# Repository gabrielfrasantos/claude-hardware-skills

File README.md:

# hardware-design-skills

**Sourced design rules and tested tools that let an AI agent design electronics in KiCad 10, from requirements to
fab files, without guessing.**

An agent asked to lay out a buck converter or pick decoupling will produce something plausible. Plausible isn't
good enough for a board: a wrong rule costs a respin. This repository gives the agent two things it lacks:

1. **Rules it can follow and you can check.** Every number cites its source (datasheet, app note, standard or fab
   capability page, by document ID and section). If a number has no source, it is marked *derived* with the
   arithmetic shown, or labelled *rule of thumb* or *house style*. Rules are vendor-neutral: they tell you which
   datasheet parameter to look up instead of copying one part family's value.
2. **Tools that work on real KiCad files.** Python scripts read and write `.kicad_sch` / `.kicad_pcb` directly and
   call `kicad-cli`. They generate the schematic, assign MCU pins, place parts, size net classes, set fab rules,
   copy vendor layouts, run gates and review the design. They run the same in an agent session, in a terminal and
   in CI.

The skills are not tied to a particular board, MCU family or vendor.

## Workflow

```mermaid
flowchart LR
  R[Requirements<br/>hardware-project] --> S[Schematic as code<br/>schematic-capture]
  S --> C[Circuit rules<br/>mcu / power / analog]
  C --> SIM[Simulation<br/>circuit-simulation]
  SIM --> P[Placement and pins<br/>pcb-placement]
  P --> N[Net classes, fab rules<br/>pcb-copper, pcb-design-rules]
  N --> L[Routing rules<br/>power / RF / high-speed / interface]
  L --> AR[Autoroute the rest<br/>pcb-routing]
  AR --> G[Gates: DRC, geometry, copper, assembly]
  G --> RV[Design review<br/>design-review + board-reviewer]
  RV --> F[Fab and assembly files<br/>hardware-project]
  V[Vendor reference layouts<br/>reference-block] -.-> P
```

Each phase ends at a gate the owner signs off. Requirements are traced to the firmware, and every decision is
logged.

## Skills

| Area | Skill | What it does |
|---|---|---|
| Project | [`hardware-project`](plugins/hardware-design/skills/hardware-project/SKILL.md) | Scaffolds a board repo (requirements traced to firmware, decision log, phase plan, reviewer agent). Checks traceability. Exports the review package, BOM, JLCPCB stock check, fab files, release package and visual diffs |
| Review | [`design-review`](plugins/hardware-design/skills/design-review/SKILL.md) | Runs every scripted check on a schematic or PCB in one command: decoupling, pull-ups, straps, voltage ratings, polarity, connector ESD, ERC/DRC, fab, geometry, net classes, assembly. A read-only reviewer agent then triages the findings against the datasheets |
| Schematic | [`schematic-capture`](plugins/hardware-design/skills/schematic-capture/SKILL.md) | Writes the schematic as Python and builds it into KiCad 10 the same way every time. Checks the netlist against intent, proves that drawing-only changes leave the circuit alone, and checks symbols against footprints and BOM fields |
| Circuits | [`mcu-circuit-design`](plugins/hardware-design/skills/mcu-circuit-design/SKILL.md) | Covers everything around any MCU: supplies, decoupling, reset/boot, clocks, debug, GPIO protection, ESD |
| | [`power-circuit-design`](plugins/hardware-design/skills/power-circuit-design/SKILL.md) | Covers input protection, buck/LDO rails, H-bridge and three-phase stages, gate drive, bus capacitors, current sensing, snubbers and thermal design |
| | [`analog-circuit-design`](plugins/hardware-design/skills/analog-circuit-design/SKILL.md) | Covers op-amps, references, ADC drive and sensor front ends: protection, noise, stability |
| | [`circuit-simulation`](plugins/hardware-design/skills/circuit-simulation/SKILL.md) | Builds an ngspice + Python suite from the schematic: loop stability, corners, transients, protection, noise, and a report |
| Layout | [`pcb-placement`](plugins/hardware-design/skills/pcb-placement/SKILL.md) | Builds or updates the board from the schematic without KiCad's window, places unlocked parts around the owner's locked anchors with simulated annealing, gates the result against assembly rules, and assigns MCU pins from the placement |
| | [`pcb-routing`](plugins/hardware-design/skills/pcb-routing/SKILL.md) | Autoroutes the non-critical nets with Freerouting, headless: writes the board as a Specctra DSN (no pcbnew), runs the router, adds its tracks and vias back |
| | [`pcb-copper`](plugins/hardware-design/skills/pcb-copper/SKILL.md) | Applies one standard net-class set (`PWR_4A`, `GND`, `DIFF_90`, `RF_50`, …). Sizes widths from current and clearances from voltage (IPC-2152 / IPC-2221) |
| | [`pcb-design-rules`](plugins/hardware-design/skills/pcb-design-rules/SKILL.md) | Sets board rules from fab profiles (JLCPCB, Seeed), turns on teardrops, records the stack-up, and gates shorts, clearance, geometry and copper. Keeps the silkscreen to readable references only |
| | [`power-pcb-layout`](plugins/hardware-design/skills/power-pcb-layout/SKILL.md) | Covers hot loops, gate drive, high-current copper, Kelvin sensing, thermal and isolation |
| | [`rf-layout`](plugins/hardware-design/skills/rf-layout/SKILL.md) | Covers 2.4 GHz radios (BLE, 802.15.4, Wi-Fi), chip-down or module: 50 Ω lines, matching, antennas, coexistence, certification |
| | [`high-speed-digital-layout`](plugins/hardware-design/skills/high-speed-digital-layout/SKILL.md) | Covers QSPI, SDRAM, DDR, SD/eMMC, RGB/MIPI/LVDS displays, cameras and clocks |
| | [`interface-layout`](plugins/hardware-design/skills/interface-layout/SKILL.md) | Covers USB, USB-C/PD, CAN, RS-485, Ethernet, isolated buses, connector ESD and shielding |
| | [`reference-block`](plugins/hardware-design/skills/reference-block/SKILL.md) | Copies a vendor's proven layout block (RF corner, NFC coil, power stage) onto your board, maps parts and nets, and checks the block stays intact |

## Install

The skills are packaged as a [Claude Code](https://code.claude.com) plugin marketplace (`hardware-skills`, one
plugin: `hardware-design`).

```
/plugin marketplace add gabrielfrasantos/hardware-design-skills
/plugin install hardware-design@hardware-skills
```

Skills load when a task matches their description. To call one by name, use e.g.
`/hardware-design:pcb-placement`. Releases are tagged `vX.Y.Z` (see the [changelog](CHANGELOG.md)). To update, run
`/plugin marketplace update hardware-skills`.

**For a whole team:** from the board repo's root, run this once and commit the `.claude/settings.json` it writes:

```bash
claude plugin marketplace add gabrielfrasantos/hardware-design-skills --scope project
```

**Other agents and plain use:** each skill is a `SKILL.md` (Markdown with YAML front matter) plus `scripts/`. The
rules-only skills (`*-circuit-design`, `*-layout`, `circuit-simulation`) are self-contained: zip the folder for
claude.ai, or point any agent that reads Agent Skills at it. The scripts are ordinary command-line tools with
`--help`. They don't need an agent.

## Quick start

The flow for a new board, as commands. In an agent session, ask for each step in words ("scaffold a board repo for a
motor controller", "review the board"), and the matching skill runs the same scripts. `$HW` is the absolute path
of `plugins/hardware-design/skills` in a checkout of this repository, so the commands still work after `cd` into the
board repo.

```bash
HW="$(pwd)/plugins/hardware-design/skills"   # run from the root of this repository's checkout

# 1. A board repo with requirements, decisions, phase gates and a reviewer agent
python3 $HW/hardware-project/scripts/scaffold.py ../my-board --name my-board --title "my-board: what it is" \
        --firmware owner/my-firmware --fab jlcpcb --layers 4
cd ../my-board            # then create hardware/my-board/my-board.kicad_pro in KiCad

# 2. Schematic as code, checked against the intended netlist
python3 $HW/schematic-capture/scripts/schgen.py build scripts/schgen/config.py
python3 $HW/schematic-capture/scripts/schgen.py check scripts/schgen/config.py

# 3. Net classes and fab rules on the KiCad project
python3 $HW/pcb-copper/scripts/netclasses.py apply hardware/my-board/my-board.kicad_pro
python3 $HW/pcb-design-rules/scripts/pcb_rules.py apply hardware/my-board/my-board.kicad_pro --fab jlcpcb --netclasses

# 4. Board from the schematic (no KiCad window needed), placement around your locked anchors, then the gates
python3 $HW/pcb-placement/scripts/sync.py hardware/my-board/my-board.kicad_pcb
python3 $HW/pcb-placement/scripts/place.py optimize hardware/my-board/my-board.kicad_pcb
python3 $HW/pcb-placement/scripts/place.py gate hardware/my-board/my-board.kicad_pcb
python3 $HW/pcb-routing/scripts/route.py run hardware/my-board/my-board.kicad_pcb --fetch --skip-nets 'GND|VM'   # after the critical nets
python3 $HW/pcb-design-rules/scripts/pcb_rules.py check hardware/my-board/my-board.kicad_pcb --report pcb-quality.md

# 5. Review everything into one findings file, then export for the fab
python3 $HW/design-review/scripts/review.py hardware/my-board --voltage VBAT=12.6
python3 $HW/hardware-project/scripts/export_jlcpcb.py
```

The generated `AGENTS.md` (imported by `CLAUDE.md`) lists every command and which skill covers each part of the
work.

## Worked example

[`examples/stepper-ble`](examples/stepper-ble/README.md) is a public board designed end to end with these skills: a
24 V stepper driver (DRV8711, eight external FETs) with Bluetooth LE (STM32WB55CG, PCB antenna) on JLCPCB 4-layer.
It has a schematic as code, the parts chosen from JLCPCB stock, the placement and MCU pin map, and every gate and the
design review run on it. It is placed but not routed. CI rebuilds its schematic and runs every gate on it with
KiCad 10 on each pull request, so the claims above can be checked on a board anyone can open.

## Requirements

| For | Needs |
|---|---|
| The tools | Python 3.10+, `pip install -r requirements.txt` (shapely, numpy, scipy, matplotlib) |
| DRC, ERC, netlists, imports, exports | KiCad **10 or later** (`kicad-cli`). Older files are refused: open and save them in KiCad 10 first |
| `circuit-simulation` | ngspice |
| `jlc_stock.py`, `fetch_datasheet.py` | Network access (JLCPCB/LCSC) |
| The test suite | None of the above beyond Python: tests use synthetic KiCad 10 files |

## How it's checked

- **Sources.** Each skill ends with its references.
  [`docs/research/best-practices-audit.md`](docs/research/best-practices-audit.md) audits the skills against
  primary sources and records what changed as a result.
- **Tests.** Every script has self-tests. CI runs them, a lint and the plugin validator on every pull request.
- **KiCad in CI.** The `example-board` job installs KiCad 10 with
  [kicad-bot](https://github.com/embedded-pro/kicad-bot) (ERC and DRC), rebuilds the example's schematic, checks it is
  the same circuit as the committed one, and runs every gate on the board.
- **Real boards.** The tools were measured on real boards (a power supply, a 50 V motor driver and a
  battery-powered robot controller). Each skill says what was measured, on what kind of board, and what wasn't.
- **Evals.** [`evals/`](evals/README.md) is a generic harness. It runs a board repo's own eval cases with and
  without the skills, scores the results against the owner's work, and plants known defects to score a review.
  Cases live in the board repos, not here.

## Status and limits

Version 0.x. The rules and tools are usable. The plan and its open phases are in [`docs/design.md`](docs/design.md).
Known limits:

- KiCad 10+ only. No KiCad 8/9 support, and no `pcbnew` (SWIG) code.
- Fab profiles exist for JLCPCB and Seeed only. Assembly rules exist for JLCPCB only. Other fabs need a profile in
  `pcb-design-rules/profiles/`.
- The RF rules cover 2.4 GHz only.
- Routing critical nets stays with the designer. `pcb-routing` autoroutes only the rest, with Freerouting (Java 25),
  and its result follows clearance and width, not the house style: expect hand tidying.
- `kicad-cli` has no *Update PCB from Schematic*; `pcb-placement`'s `sync.py` does it headless. It adds, updates,
  replaces and removes footprints and pad nets, matched to symbols by their link. It refuses to replace a footprint
  on the back side, and leaves outline, zones, net classes and copper on renamed nets (`pcb-design-rules`'
  `orphan_copper_nets`) to other tools or KiCad. The example board was first built with a short `pcbnew` script;
  `sync.py` reproduces it byte for byte (`pcb-placement` §0).
- Some IPC values are transcribed from secondary sources until the standards themselves are checked. Each skill
  marks which ones.

## Repository layout

```
.claude-plugin/marketplace.json        marketplace "hardware-skills"
plugins/hardware-design/
├── .claude-plugin/plugin.json         plugin "hardware-design"
├── agents/board-reviewer.md           read-only reviewer agent
└── skills/<skill>/                    SKILL.md, plus scripts/ and profiles/ where the skill has tools
docs/design.md                         plan and decisions (D1, D2, ...)
docs/research/                         audits and research notes
evals/                                 generic eval harness
```

## Contributing

Security issues: see [SECURITY.md](SECURITY.md).

The most useful contribution is a correction backed by a primary source. See [CONTRIBUTING.md](CONTRIBUTING.md) for
how rules are sourced, how scripts are tested and how commits become releases.

## License

[MIT](LICENSE). The skills cite vendor documents and standards without reproducing them; those documents remain
under their owners' terms. Vendor design files used with `reference-block` stay in your board repo's gitignored
`reference/` folder, under the vendor's licence.

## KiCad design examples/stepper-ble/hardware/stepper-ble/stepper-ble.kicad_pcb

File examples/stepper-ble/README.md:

# stepper-ble

A 24 V bipolar stepper driver with Bluetooth LE, designed from scratch with the `hardware-design` skills of this
repository and nothing else: the worked example. It is **placed, not routed** (D-027).

| | |
|---|---|
| Input | 24 V nominal, 30 V max, 2-pin terminal; 3 A fast fuse, reverse-polarity N-FET, SMAJ33A clamp |
| Motor | one bipolar stepper, 2.0 A peak per phase: DRV8711 + 8 x CSD18543Q3A, 0.1 ohm low-side sense, stall detection, NTC on the FETs |
| Logic | LMR36510 5 V buck OR-ed with USB VBUS, AP2112K 3.3 V |
| MCU, radio | STM32WB55CGU6 (SMPS mode, 32 MHz HSE, 32.768 kHz LSE), MLPF-WB55-01E3, TI SWRA117D PCB antenna with a DNP tuning pi |
| Interfaces | USB-C 2.0 full-speed sink with USBLC6, SWD on a Tag-Connect TC2030 land, two LEDs, a button |
| Board | 80 x 60 mm, 4 layers SIG/GND/GND/SIG (JLC04161H-7628, 1.6 mm), JLCPCB fab and assembly, IPC Class 2, 106 parts |

Contract: `docs/requirements.md` (26 requirements); intent: `docs/decisions.md` (27 decisions); status:
`docs/plan.md`. Every value on the schematic carries its source in a note on its sheet.

## Layout of this folder

```
scripts/make_library.py     project library: DRV8711 and MLPF symbols, MLPF land, two adapted KiCad footprints (D-016)
scripts/schgen/             the schematic as code: config.py, design/<sheet>.py, parts.py (the BOM), expected.json
scripts/make_board.py       board from KiCad's netlist with pcbnew: build/update, outline, stack-up, zones, placement
pin-data/                   pin-needs.txt (from the requirements, D-017) and pinmap.txt (pins.py, frozen D-014)
hardware/stepper-ble/       KiCad 10 project; placement-baseline.json is the accepted placement's gate metrics
bom/                        bom.csv, bom_jlc.csv (export_bom.py)
```

## Reproduce

From this folder, with KiCad 10 (`kicad-cli` and its `pcbnew` Python module) and `pip install -r ../../requirements.txt`:

```bash
HW=../../plugins/hardware-design/skills
export HW_PROJECT_ROOT=$PWD                    # the hardware-project scripts otherwise take the repository root
python3 scripts/make_library.py
python3 $HW/schematic-capture/scripts/schgen.py build scripts/schgen/config.py
python3 $HW/schematic-capture/scripts/schgen.py check scripts/schgen/config.py
python3 $HW/pcb-copper/scripts/netclasses.py assign hardware/stepper-ble/stepper-ble.kicad_pro
/usr/bin/python3 scripts/make_board.py build   # needs pcbnew: system Python
/usr/bin/python3 scripts/make_board.py place
python3 $HW/pcb-design-rules/scripts/pcb_rules.py apply hardware/stepper-ble/stepper-ble.kicad_pro --fab jlcpcb --netclasses
python3 $HW/pcb-copper/scripts/netclasses.py apply hardware/stepper-ble/stepper-ble.kicad_pro
python3 $HW/pcb-design-rules/scripts/silk.py apply hardware/stepper-ble/stepper-ble.kicad_pcb
```

The pin map was found with `pins.py assign ... --out pin-data/pinmap.txt` after a first placement; the schematic
reads it, so a second `build` / `make_board.py build` / `place` closes the loop (pcb-placement §5). The impedance
classes' widths (D-025) were written into the `.kicad_pro` by hand after `netclasses.py apply`.

## Gates

The CI job `example-board` runs these. Results on 2026-11-22, KiCad 10.0.8:

| Gate | Result |
|---|---|
| `schgen.py build` | 7 sheets, 106 parts, layout lint 0 |
| `schgen.py check` | netlist matches intent, 77 nets |
| KiCad ERC | 0 violations |
| `sync.py --check` | the board is in step with the schematic (no footprint would change) |
| `library_check.py` | PASS (no pin without pad, no pad without pin, every BOM part with LCSC and MPN) |
| `pcb_rules.py check --allow-unrouted --gate zone_islands=2` | PASS: 0 shorts, 0 clearance, 0 below fab minimum, 0 DRC errors, schematic parity 0 errors; soft: `gnd_via_max_distance_mm` (no vias yet) |
| `netclasses.py check` | PASS |
| `silk.py check` | PASS; KiCad DRC reports no silkscreen findings |
| `place.py gate --enforce --baseline` | valid, ratios 1.00; assembly spacing 0; ratsnest 1475 mm, 231 crossings |
| `pins.py check --mcu U401` | PASS, 21 of 21 functions |
| `trace.py` | PASS, 26 requirements, 27 decisions |
| `review.py --allow-unrouted --voltage VM=30 --voltage VIN_RAW=30` | 0 BLOCKER, 0 MAJOR, 12 MINOR, 3 NOTE |
| `jlc_stock.py bom/bom.csv --boards 5` (not in CI) | 0 problems; 44 lines, 28 extended parts |

The board is not routed, so `--allow-unrouted` leaves KiCad's unconnected items out. The MINORs are DC-bias screening on the 50 V and 6.3 V MLCCs (D-004, OI-4) and connector nets
without an ESD part (VIN_N, CC1/CC2, the TC2030 land: D-003, D-008, D-009).

## What was not checked

- **Nothing is routed**: no hot loop, Kelvin pair, RF line, USB pair or stitching exists yet; the layout rules that
  need copper (power-pcb-layout §3-§5, rf-layout §2, interface-layout §3-§4) are only prepared by the placement.
- **No simulation** (S1 input transients, S2 current regulation): D-004 (50 V capacitors under the 53.3 V clamp) and
  D-013 (phase-pin negative swing, no clamps) are open risks.
- **Impedance widths** are derived from closed forms, not JLCPCB's calculator (D-025, OI-1).
- **Footprint checks by eye**: the MLPF land against DS12804 Fig. 13 and the adapted NexFET land against SLPS633 §7.2
  were written from the drawings; neither was compared on a printed board. `jlc_stock.py` could not compare 13
  package names automatically (listed as "check by hand").
- **Terminal-block orientation**: the wire entry is taken to be the footprint's +y side (from its fab drawing); the
  3D models were not installed, so no render confirmed it.
- **L201 saturation current** (OI-3) and the DRV8711 V5 capacitor value (OI-5) are unresolved datasheet questions.
- **The reviewer agent** (`.claude/agents/stepper-ble-board-reviewer.md`) has not reviewed the board; `review.py`'s
  scripted checks have.
- **Reversed 24 V with USB connected** is not protected (D-003).
- No gate is signed off by an owner (`docs/plan.md`).

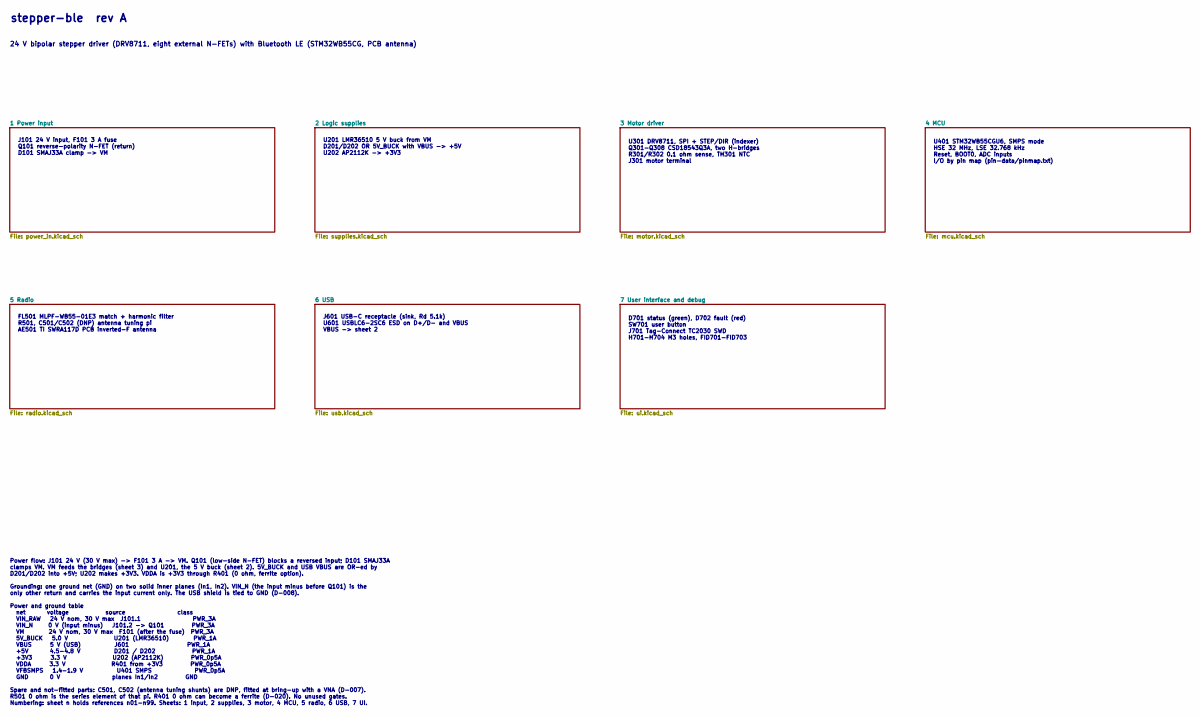
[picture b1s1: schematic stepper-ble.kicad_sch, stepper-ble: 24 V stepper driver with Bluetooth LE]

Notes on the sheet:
U301 DRV8711, SPI + STEP/DIR (indexer) Q301-Q308 CSD18543Q3A, two H-bridges R301/R302 0.1 ohm sense, TH301 NTC J301 motor terminal
D701 status (green), D702 fault (red) SW701 user button J701 Tag-Connect TC2030 SWD H701-H704 M3 holes, FID701-FID703
FL501 MLPF-WB55-01E3 match + harmonic filter R501, C501/C502 (DNP) antenna tuning pi AE501 TI SWRA117D PCB inverted-F antenna
U201 LMR36510 5 V buck from VM D201/D202 OR 5V_BUCK with VBUS -> +5V U202 AP2112K -> +3V3
24 V bipolar stepper driver (DRV8711, eight external N-FETs) with Bluetooth LE (STM32WB55CG, PCB antenna)
J101 24 V input, F101 3 A fuse Q101 reverse-polarity N-FET (return) D101 SMAJ33A clamp -> VM
stepper-ble rev A
U401 STM32WB55CGU6, SMPS mode HSE 32 MHz, LSE 32.768 kHz Reset, BOOT0, ADC inputs I/O by pin map (pin-data/pinmap.txt)
Power flow: J101 24 V (30 V max) -> F101 3 A -> VM. Q101 (low-side N-FET) blocks a reversed input; D101 SMAJ33A clamps VM. VM feeds the bridges (sheet 3) and U201, the 5 V buck (sheet 2). 5V_BUCK and USB VBUS are OR-ed by D201/D202 into +5V; U202 makes +3V3. VDDA is +3V3 through R401 (0 ohm, ferrit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
J601 USB-C receptacle (sink, Rd 5.1k) U601 USBLC6-2SC6 ESD on D+/D- and VBUS VBUS -> sheet 2

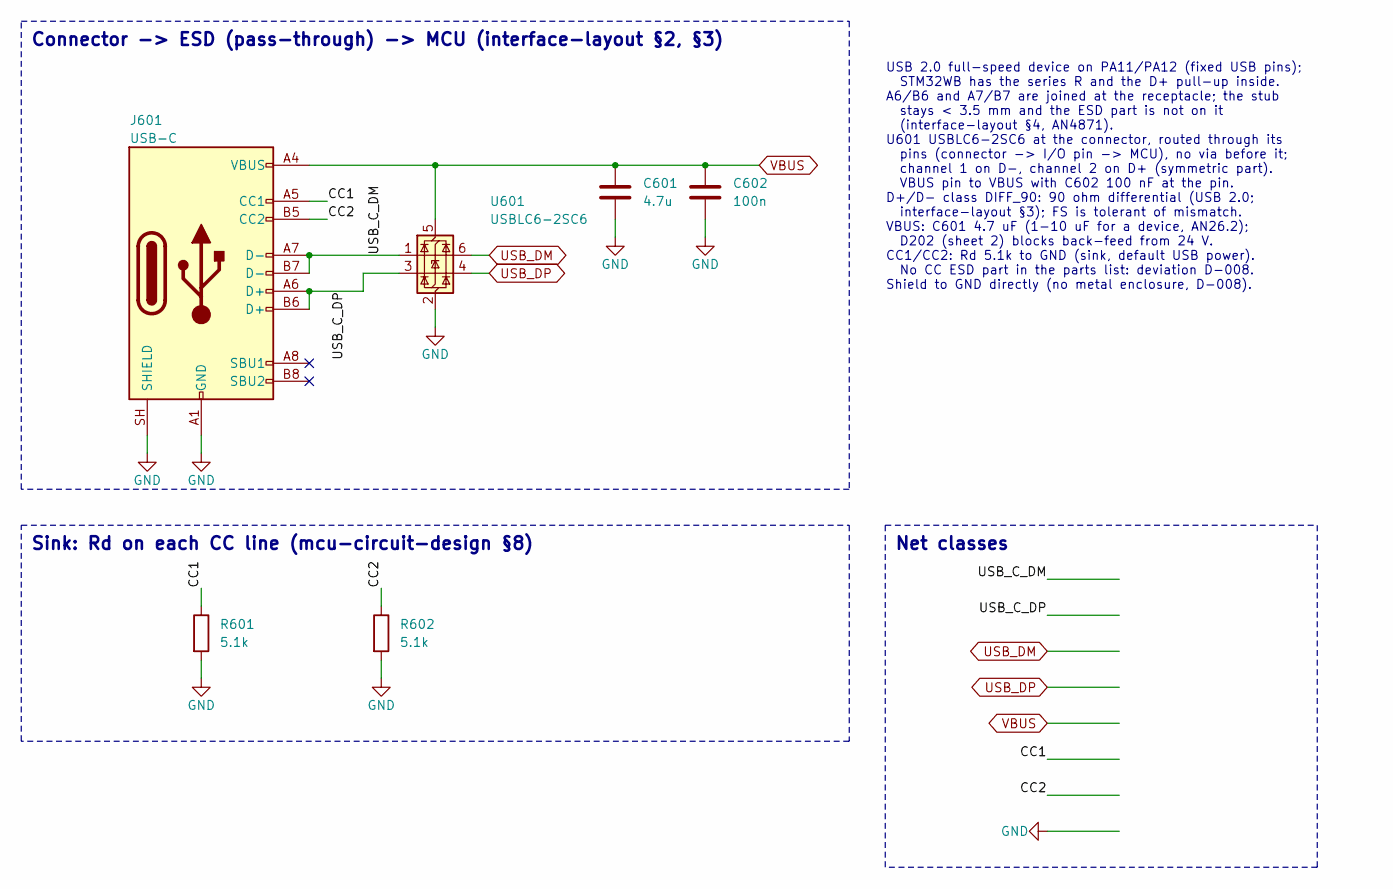
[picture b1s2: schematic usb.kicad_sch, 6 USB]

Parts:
C601: 4.7u; C_0402_1005Metric; Voltage 10V; MPN CL05A475MP5NRNC; LCSC C23733
C602: 100n; C_0402_1005Metric; Voltage 16V; MPN CL05B104KO5NNNC; LCSC C1525
J601: USB-C; USB_C_Receptacle_HRO_TYPE-C-31-M-12; MPN TYPE-C-31-M-12; LCSC C165948
R601, R602: 5.1k; R_0402_1005Metric; MPN 0402WGF5101TCE; LCSC C25905
U601: USBLC6-2SC6; SOT-23-6; MPN USBLC6-2SC6; LCSC C7519

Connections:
/6 USB/CC1: J601.A5 (CC1), R601.1
/6 USB/CC2: J601.B5 (CC2), R602.1
/6 USB/USB_C_DM: J601.A7 (D-), J601.B7 (D-), U601.1 (I/O1)
/6 USB/USB_C_DP: J601.A6 (D+), J601.B6 (D+), U601.3 (I/O2)
GND: C601.2, C602.2, J601.A1 (GND), J601.A12 (GND), J601.B1 (GND), J601.B12 (GND), J601.SH (SHIELD), R601.2, R602.2, U601.2 (GND); also elsewhere on the board
USB_DM: U601.6 (I/O1); also elsewhere on the board
USB_DP: U601.4 (I/O2); also elsewhere on the board
VBUS: C601.1, C602.1, J601.A4 (VBUS), J601.A9 (VBUS), J601.B4 (VBUS), J601.B9 (VBUS), U601.5 (VBUS); also elsewhere on the board

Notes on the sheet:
USB 2.0 full-speed device on PA11/PA12 (fixed USB pins); STM32WB has the series R and the D+ pull-up inside. A6/B6 and A7/B7 are joined at the receptacle; the stub stays < 3.5 mm and the ESD part is not on it (interface-layout §4, AN4871). U601 USBLC6-2SC6 at the connector, routed through its pins 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
Sink: Rd on each CC line (mcu-circuit-design §8)
Net classes
Connector -> ESD (pass-through) -> MCU (interface-layout §2, §3)

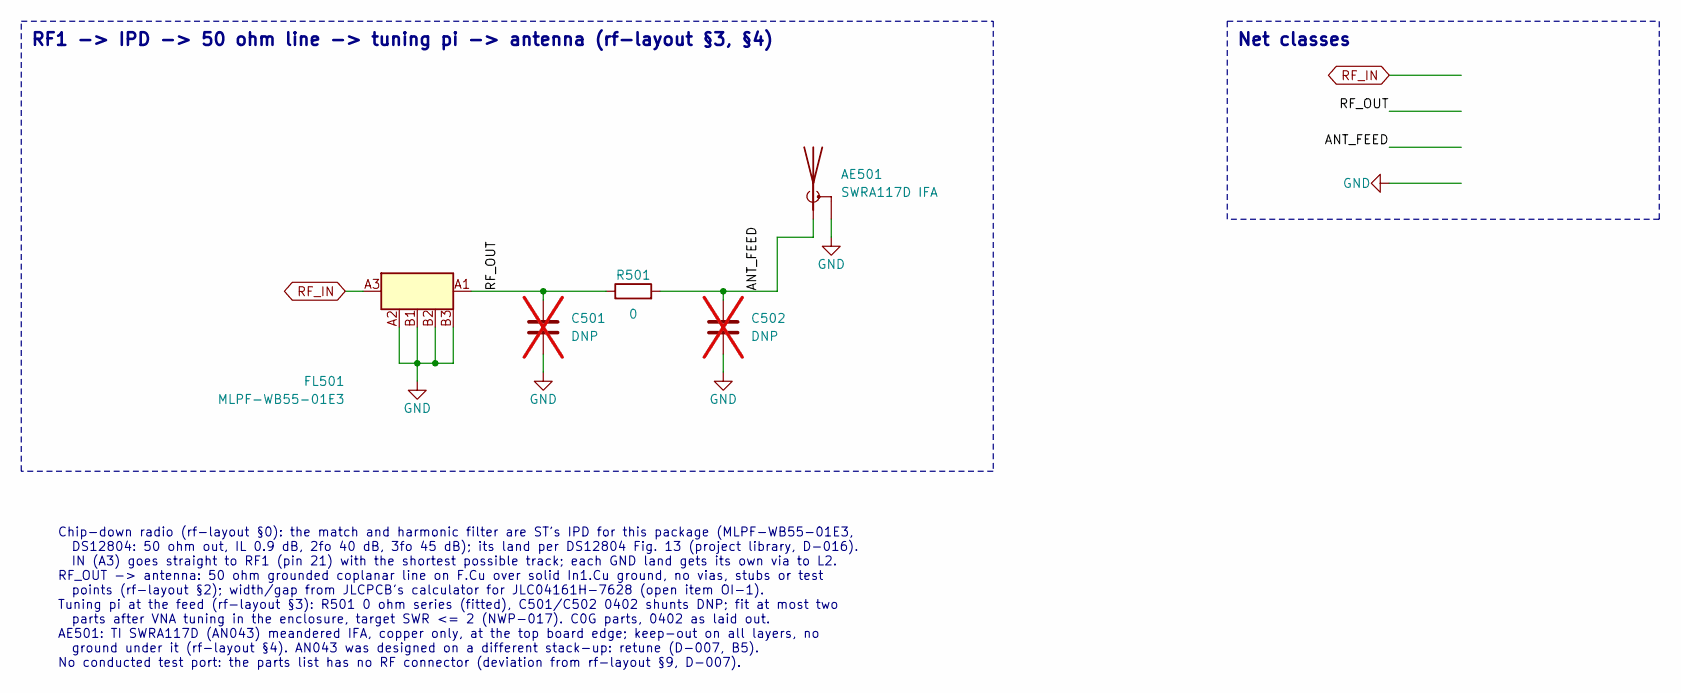
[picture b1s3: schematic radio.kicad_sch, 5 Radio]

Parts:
AE501: SWRA117D IFA; Texas_SWRA117D_2.4GHz_Left_Drill0.2
C501, C502: DNP; C_0402_1005Metric; not fitted
FL501: MLPF-WB55-01E3; MLPF-WB55-01E3_CSP-6_1.0x1.6mm; MPN MLPF-WB55-01E3; LCSC C2651048
R501: 0; R_0402_1005Metric; MPN 0402WGF0000TCE; LCSC C17168

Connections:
/5 Radio/ANT_FEED: AE501.1 (A), C502.1, R501.2
/5 Radio/RF_OUT: C501.1, FL501.A1 (OUT), R501.1
GND: AE501.2 (Shield), C501.2, C502.2, FL501.A2 (GND4), FL501.B1 (GND3), FL501.B2 (GND2), FL501.B3 (GND1); also elsewhere on the board
RF_IN: FL501.A3 (IN); also elsewhere on the board

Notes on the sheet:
RF1 -> IPD -> 50 ohm line -> tuning pi -> antenna (rf-layout §3, §4)
Net classes
Chip-down radio (rf-layout §0): the match and harmonic filter are ST's IPD for this package (MLPF-WB55-01E3, DS12804: 50 ohm out, IL 0.9 dB, 2fo 40 dB, 3fo 45 dB); its land per DS12804 Fig. 13 (project library, D-016). IN (A3) goes straight to RF1 (pin 21) with the shortest possible track; each GND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

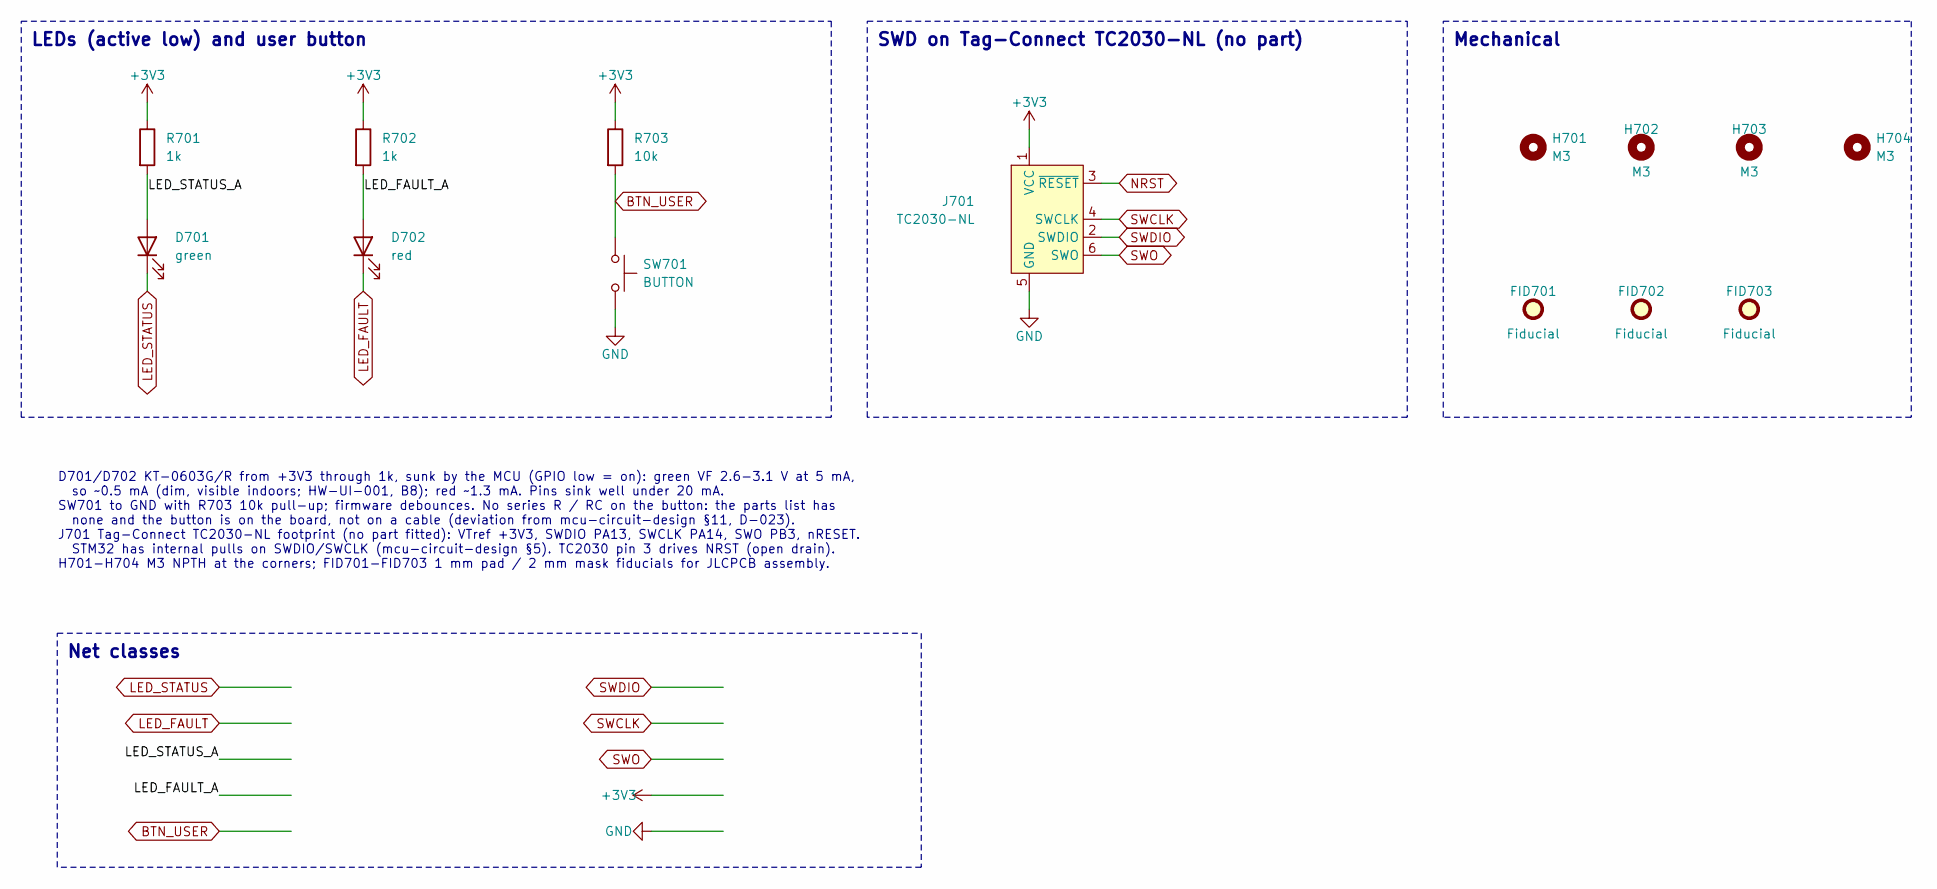
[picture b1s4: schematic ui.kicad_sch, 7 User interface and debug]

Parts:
D701: green; LED_0603_1608Metric; MPN KT-0603G; LCSC C12624
D702: red; LED_0603_1608Metric; MPN KT-0603R; LCSC C2286
FID701, FID702, FID703: Fiducial; Fiducial_1mm_Mask2mm
H701, H702, H703, H704: M3; MountingHole_3.2mm_M3
J701: TC2030-NL; Tag-Connect_TC2030-IDC-NL_2x03_P1.27mm_Vertical
R701, R702: 1k; R_0402_1005Metric; MPN 0402WGF1001TCE; LCSC C11702
R703: 10k; R_0402_1005Metric; MPN 0402WGF1002TCE; LCSC C25744
SW701: BUTTON; SW_Push_1P1T_XKB_TS-1187A; MPN TS-1187A-B-A-B; LCSC C318884

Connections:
+3V3: J701.1 (VCC), R701.1, R702.1, R703.1; also elsewhere on the board
/7 User interface and debug/LED_FAULT_A: D702.2 (A), R702.2
/7 User interface and debug/LED_STATUS_A: D701.2 (A), R701.2
BTN_USER: R703.2, SW701.1; also elsewhere on the board
GND: J701.5 (GND), SW701.2; also elsewhere on the board
LED_FAULT: D702.1 (K); also elsewhere on the board
LED_STATUS: D701.1 (K); also elsewhere on the board
NRST: J701.3 (~RESET); also elsewhere on the board
SWCLK: J701.4 (SWCLK); also elsewhere on the board
SWDIO: J701.2 (SWDIO); also elsewhere on the board
SWO: J701.6 (SWO); also elsewhere on the board

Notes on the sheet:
SWD on Tag-Connect TC2030-NL (no part)
Mechanical
D701/D702 KT-0603G/R from +3V3 through 1k, sunk by the MCU (GPIO low = on): green VF 2.6-3.1 V at 5 mA, so ~0.5 mA (dim, visible indoors; HW-UI-001, B8); red ~1.3 mA. Pins sink well under 20 mA. SW701 to GND with R703 10k pull-up; firmware debounces. No series R / RC on the button: the parts list h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
LEDs (active low) and user button
Net classes

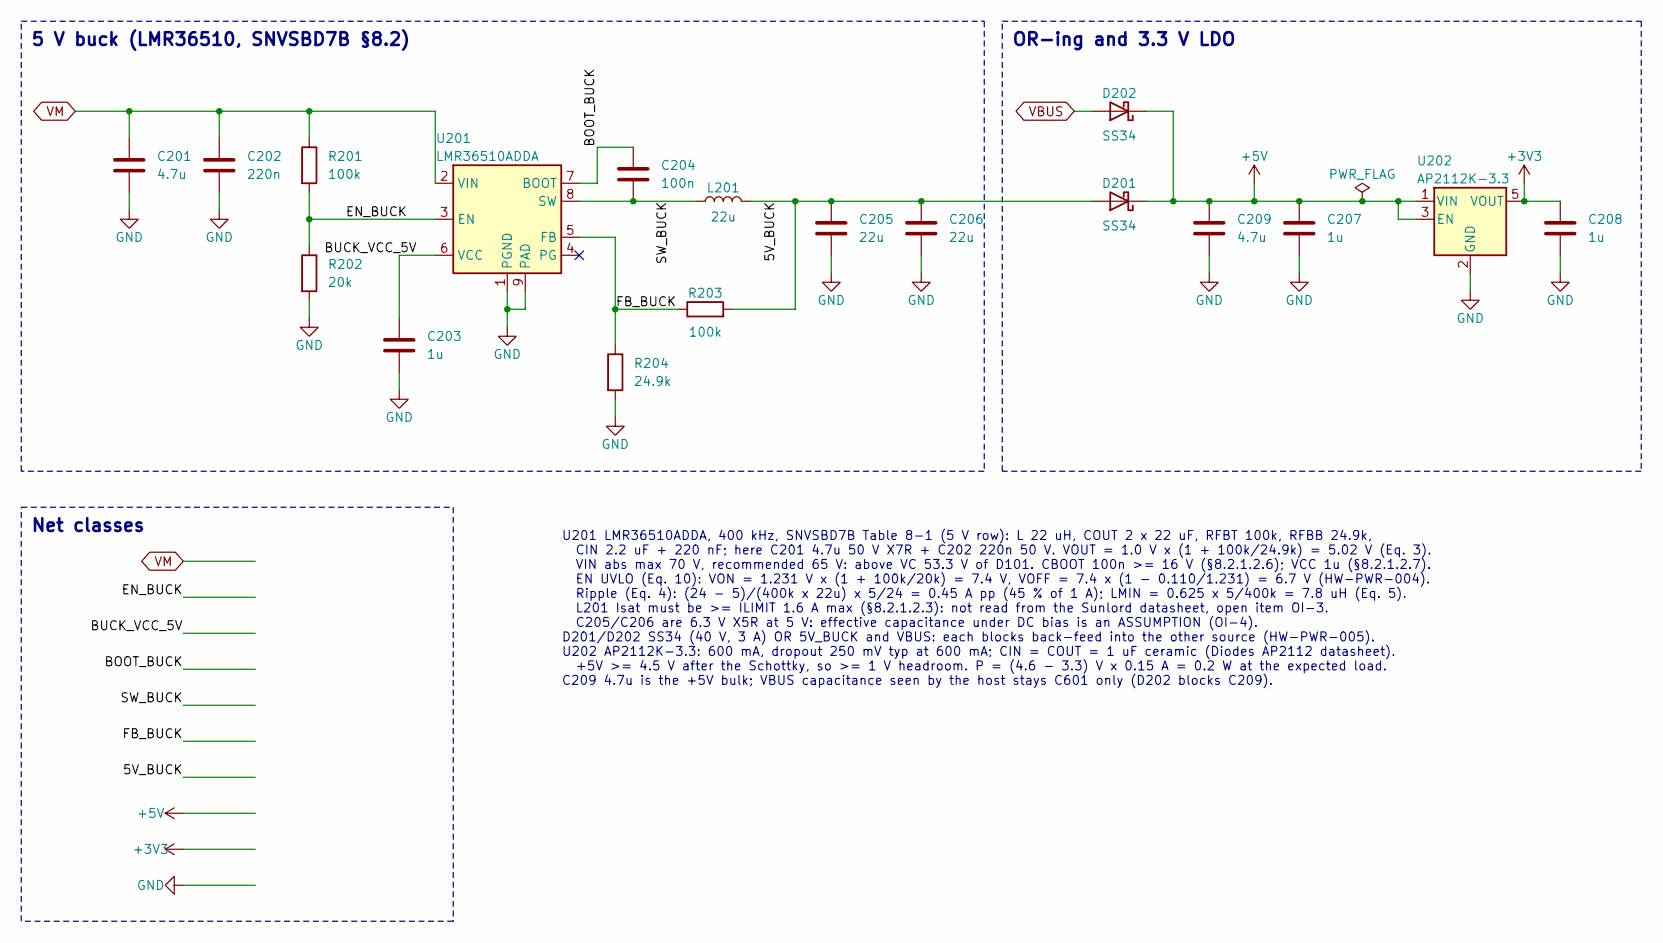
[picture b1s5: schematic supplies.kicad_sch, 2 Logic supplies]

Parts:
C201: 4.7u; C_1206_3216Metric; Voltage 50V; MPN CL31B475KBHNNNE; LCSC C51205
C202: 220n; C_0603_1608Metric; Voltage 50V; MPN CL10B224KB8NNNC; LCSC C64705
C203, C207, C208: 1u; C_0402_1005Metric; Voltage 25V; MPN CL05A105KA5NNNC; LCSC C16193167
C204: 100n; C_0402_1005Metric; Voltage 16V; MPN CL05B104KO5NNNC; LCSC C1525
C205, C206: 22u; C_0805_2012Metric; Voltage 6.3V; MPN CL21A226MQQNNNE; LCSC C5674
C209: 4.7u; C_0402_1005Metric; Voltage 10V; MPN CL05A475MP5NRNC; LCSC C23733
D201, D202: SS34; D_SMA; MPN SS34; LCSC C8678
L201: 22u; L_Sunlord_SWPA4030S; MPN SWPA4030S220MT; LCSC C83472
R201, R203: 100k; R_0402_1005Metric; MPN 0402WGF1003TCE; LCSC C25741
R202: 20k; R_0402_1005Metric; MPN 0402WGF2002TCE; LCSC C25765
R204: 24.9k; R_0402_1005Metric; MPN 0402WGF2492TCE; LCSC C25874
U201: LMR36510ADDA; Texas_HTSOP-8-1EP_3.9x4.9mm_P1.27mm_EP2.95x4.9mm_Mask2.4x3.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; MPN LMR36510ADDAR; LCSC C1858393
U202: AP2112K-3.3; SOT-23-5; MPN AP2112K-3.3TRG1; LCSC C51118

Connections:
+3V3: C208.1, U202.5 (VOUT); also elsewhere on the board
+5V: C207.1, C209.1, D201.1 (K), D202.1 (K), U202.1 (VIN), U202.3 (EN)
/2 Logic supplies/5V_BUCK: C205.1, C206.1, D201.2 (A), L201.2, R203.2
/2 Logic supplies/BOOT_BUCK: C204.1, U201.7 (BOOT)
/2 Logic supplies/BUCK_VCC_5V: C203.1, U201.6 (VCC)
/2 Logic supplies/EN_BUCK: R201.2, R202.1, U201.3 (EN)
/2 Logic supplies/FB_BUCK: R203.1, R204.1, U201.5 (FB)
/2 Logic supplies/SW_BUCK: C204.2, L201.1, U201.8 (SW)
GND: C201.2, C202.2, C203.2, C205.2, C206.2, C207.2, C208.2, C209.2, R202.2, R204.2, U201.1 (PGND), U201.9 (PAD), U202.2 (GND); also elsewhere on the board
VBUS: D202.2 (A); also elsewhere on the board
VM: C201.1, C202.1, R201.1, U201.2 (VIN); also elsewhere on the board

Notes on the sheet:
OR-ing and 3.3 V LDO
5 V buck (LMR36510, SNVSBD7B §8.2)
U201 LMR36510ADDA, 400 kHz, SNVSBD7B Table 8-1 (5 V row): L 22 uH, COUT 2 x 22 uF, RFBT 100k, RFBB 24.9k, CIN 2.2 uF + 220 nF; here C201 4.7u 50 V X7R + C202 220n 50 V. VOUT = 1.0 V x (1 + 100k/24.9k) = 5.02 V (Eq. 3). VIN abs max 70 V, recommended 65 V: above VC 53.3 V of D101. CBOOT 100n >= 16 V 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
Net classes

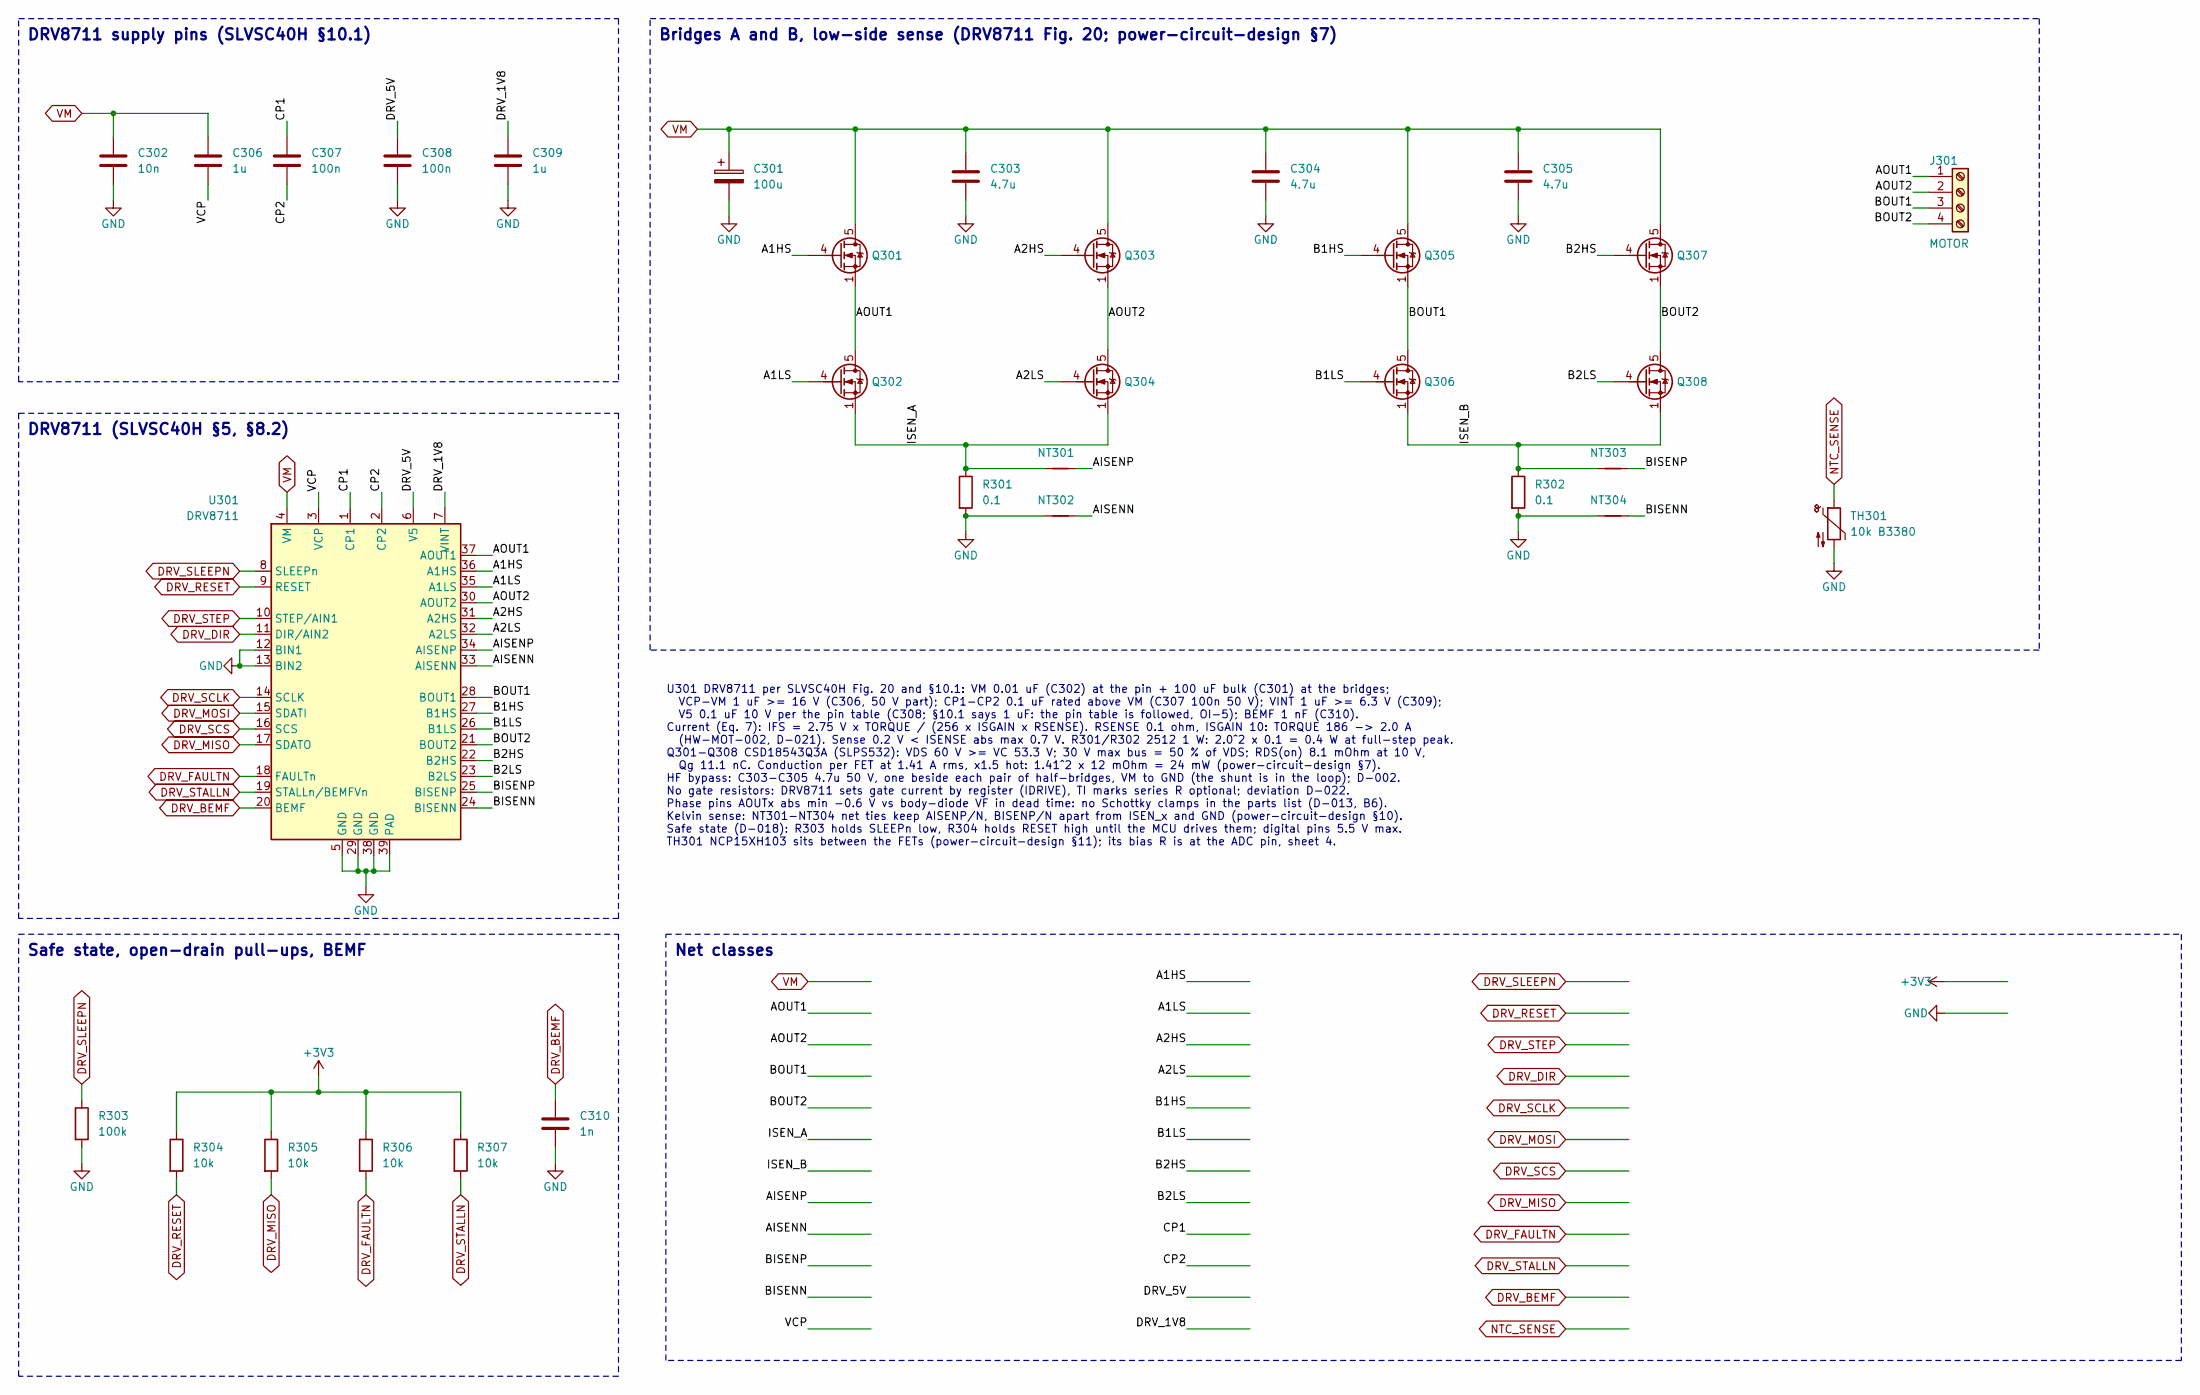
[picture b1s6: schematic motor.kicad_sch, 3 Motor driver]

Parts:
C301: 100u; CP_Elec_8x10; Voltage 50V; MPN RVT1H101M0810; LCSC C72480
C302: 10n; C_0402_1005Metric; Voltage 50V; MPN CL05B103KB5NNNC; LCSC C15195
C303, C304, C305: 4.7u; C_1206_3216Metric; Voltage 50V; MPN CL31B475KBHNNNE; LCSC C51205
C306: 1u; C_0603_1608Metric; Voltage 50V; MPN CL10A105KB8NNNC; LCSC C15849
C307: 100n; C_0603_1608Metric; Voltage 50V; MPN CL10B104KB8NNNC; LCSC C1591
C308: 100n; C_0402_1005Metric; Voltage 16V; MPN CL05B104KO5NNNC; LCSC C1525
C309: 1u; C_0402_1005Metric; Voltage 25V; MPN CL05A105KA5NNNC; LCSC C16193167
C310: 1n; C_0402_1005Metric; Voltage 50V; MPN CL05B102KB5NNNC; LCSC C14442
J301: MOTOR; TerminalBlock_Phoenix_MKDS-1,5-4-5.08_1x04_P5.08mm_Horizont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; MPN 1715747; LCSC C5443561
NT301, NT302, NT303, NT304: NetTie; NetTie-2_SMD_Pad0.5mm
Q301, Q302, Q303, Q304, Q305, Q306, Q307, Q308: CSD18543Q3A; VSON-8_3.3x3.3mm_P0.65mm_NexFET_TI-land; Voltage 60V; MPN CSD18543Q3A; LCSC C840100
R301, R302: 0.1; R_2512_6332Metric; MPN 25121WF100LT4E; LCSC C25466
R303: 100k; R_0402_1005Metric; MPN 0402WGF1003TCE; LCSC C25741
R304, R305, R306, R307: 10k; R_0402_1005Metric; MPN 0402WGF1002TCE; LCSC C25744
TH301: 10k B3380; R_0402_1005Metric; MPN NCP15XH103F03RC; LCSC C77131
U301: DRV8711; HTSSOP-38-1EP_4.4x9.7mm_P0.5mm_EP2.74x4.75mm_ThermalVias; MPN DRV8711DCPR; LCSC C60013

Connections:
+3V3: R304.1, R305.1, R306.1, R307.1; also elsewhere on the board
/3 Motor driver/A1HS: Q301.4 (G), U301.36 (A1HS)
/3 Motor driver/A1LS: Q302.4 (G), U301.35 (A1LS)
/3 Motor driver/A2HS: Q303.4 (G), U301.31 (A2HS)
/3 Motor driver/A2LS: Q304.4 (G), U301.32 (A2LS)
/3 Motor driver/AISENN: NT302.2, U301.33 (AISENN)
/3 Motor driver/AISENP: NT301.2, U301.34 (AISENP)
/3 Motor driver/AOUT1: J301.1, Q301.1 (S), Q301.2 (S), Q301.3 (S), Q302.5 (D), U301.37 (AOUT1)
/3 Motor driver/AOUT2: J301.2, Q303.1 (S), Q303.2 (S), Q303.3 (S), Q304.5 (D), U301.30 (AOUT2)
/3 Motor driver/B1HS: Q305.4 (G), U301.27 (B1HS)
/3 Motor driver/B1LS: Q306.4 (G), U301.26 (B1LS)
/3 Motor driver/B2HS: Q307.4 (G), U301.22 (B2HS)
/3 Motor driver/B2LS: Q308.4 (G), U301.23 (B2LS)
/3 Motor driver/BISENN: NT304.2, U301.24 (BISENN)
/3 Motor driver/BISENP: NT303.2, U301.25 (BISENP)
/3 Motor driver/BOUT1: J301.3, Q305.1 (S), Q305.2 (S), Q305.3 (S), Q306.5 (D), U301.28 (BOUT1)
/3 Motor driver/BOUT2: J301.4, Q307.1 (S), Q307.2 (S), Q307.3 (S), Q308.5 (D), U301.21 (BOUT2)
/3 Motor driver/CP1: C307.1, U301.1 (CP1)
/3 Motor driver/CP2: C307.2, U301.2 (CP2)
/3 Motor driver/DRV_1V8: C309.1, U301.7 (VINT)
/3 Motor driver/DRV_5V: C308.1, U301.6 (V5)
/3 Motor driver/ISEN_A: NT301.1, Q302.1 (S), Q302.2 (S), Q302.3 (S), Q304.1 (S), Q304.2 (S), Q304.3 (S), R301.1
/3 Motor driver/ISEN_B: NT303.1, Q306.1 (S), Q306.2 (S), Q306.3 (S), Q308.1 (S), Q308.2 (S), Q308.3 (S), R302.1
/3 Motor driver/VCP: C306.2, U301.3 (VCP)
DRV_BEMF: C310.1, U301.20 (BEMF); also elsewhere on the board
DRV_DIR: U301.11 (DIR/AIN2); also elsewhere on the board
DRV_FAULTN: R306.2, U301.18 (FAULTn); also elsewhere on the board
DRV_MISO: R305.2, U301.17 (SDATO); also elsewhere on the board
DRV_MOSI: U301.15 (SDATI); also elsewhere on the board
DRV_RESET: R304.2, U301.9 (RESET); also elsewhere on the board
DRV_SCLK: U301.14 (SCLK); also elsewhere on the board
DRV_SCS: U301.16 (SCS); also elsewhere on the board
DRV_SLEEPN: R303.1, U301.8 (SLEEPn); also elsewhere on the board
DRV_STALLN: R307.2, U301.19 (STALLn/BEMFVn); also elsewhere on the board
DRV_STEP: U301.10 (STEP/AIN1); also elsewhere on the board
GND: C301.2, C302.2, C303.2, C304.2, C305.2, C308.2, C309.2, C310.2, NT302.1, NT304.1, R301.2, R302.2, R303.2, TH301.2, U301.5 (GND), U301.12 (BIN1), U301.13 (BIN2), U301.29 (GND), U301.38 (GND), U301.39 (PAD); also elsewhere on the board
NTC_SENSE: TH301.1; also elsewhere on the board
VM: C301.1, C302.1, C303.1, C304.1, C305.1, C306.1, Q301.5 (D), Q303.5 (D), Q305.5 (D), Q307.5 (D), U301.4 (VM); also elsewhere on the board

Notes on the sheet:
U301 DRV8711 per SLVSC40H Fig. 20 and §10.1: VM 0.01 uF (C302) at the pin + 100 uF bulk (C301) at the bridges; VCP-VM 1 uF >= 16 V (C306, 50 V part); CP1-CP2 0.1 uF rated above VM (C307 100n 50 V); VINT 1 uF >= 6.3 V (C309); V5 0.1 uF 10 V per the pin table (C308; §10.1 says 1 uF: the pin table is 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
Bridges A and B, low-side sense (DRV8711 Fig. 20; power-circuit-design §7)
DRV8711 (SLVSC40H §5, §8.2)
DRV8711 supply pins (SLVSC40H §10.1)
Net classes
Safe state, open-drain pull-ups, BEMF
